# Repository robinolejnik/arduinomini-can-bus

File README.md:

This board can be soldered with pinheaders onto an Arduino Mini. It contains the MCP2515 CAN bus controller and the MCP2551 CAN tranceiver.
The MCP2515 is connected to the hardware-SPI of the ATMega328p.

There are some jumpers:

| Jumper | Function                                                                                              |
| ------ |------------------------------------------------------------------------------------------------------ |
| TERM   | Connects an 120 Ohm bus termination to the CAN-lines.                                                 |
| SCK    | Connects the ATMega328p's clock output (Arduino pin 8/PB0/CLK0) to the MCP2515's clock input.         |
| CS     | Connects the MCP2515's chip select line to Arduino pin 10(PB2/SS).                                    |
| INT    | Connects the MCP2515's interrupt line to either Arduino pin 2 (PD2/INT0) or Arduino pin 3 (PD3/INT1). |

If you want to use other pins you can solder a wire to the jumper pad

View/Order the board on OSH Park: https://oshpark.com/shared_projects/cdqGDQ5q

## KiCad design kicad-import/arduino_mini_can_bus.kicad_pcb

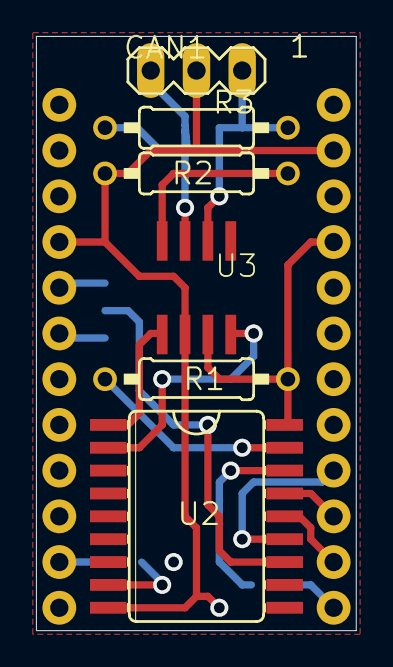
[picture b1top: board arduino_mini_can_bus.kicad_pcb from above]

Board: 2 copper layers, 17.8 x 33.0 mm, 11 parts (0 on the bottom side), 19 nets.

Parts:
CAN1: MA03-1
CS1: SJ
INT1: SJ2W; SJ_2
R1: 10k; 0207_10
R2: R-EU_0207_10; 0207_10
R3: 120; 0207_10
SCK1: SJ
TERM1: SJ
U1: ARDUINO_MINI
U2: MCP2515SO; SO18L
U3: MCP2551SN; SO-08

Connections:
/INT: INT1.2, U2.12
/SCK: SCK1.2, U2.8
unnamed: CAN1.1, R3.1, U3.6
unnamed: CAN1.3, TERM1.1, U3.7
unnamed: CS1.1, U2.16
unnamed: CS1.2, U1.13
unnamed: INT1.1, U1.5
unnamed: INT1.3, U1.6
unnamed: R1.1, U2.17
unnamed: R2.2, U3.8
unnamed: R3.2, TERM1.2
unnamed: SCK1.1, U1.11
unnamed: U1.14, U2.14
unnamed: U1.15, U2.15
unnamed: U1.16, U2.13
unnamed: U2.1, U3.1
unnamed: U2.2, U3.4
VDD: R1.2, U1.21, U2.18, U3.3
VSS: CAN1.2, R2.1, U1.4, U1.23, U2.9, U3.2

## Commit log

2016-04-17 Added eagle files and Readme
2021-10-12 Added converted KiCad-files and PDF schematic
